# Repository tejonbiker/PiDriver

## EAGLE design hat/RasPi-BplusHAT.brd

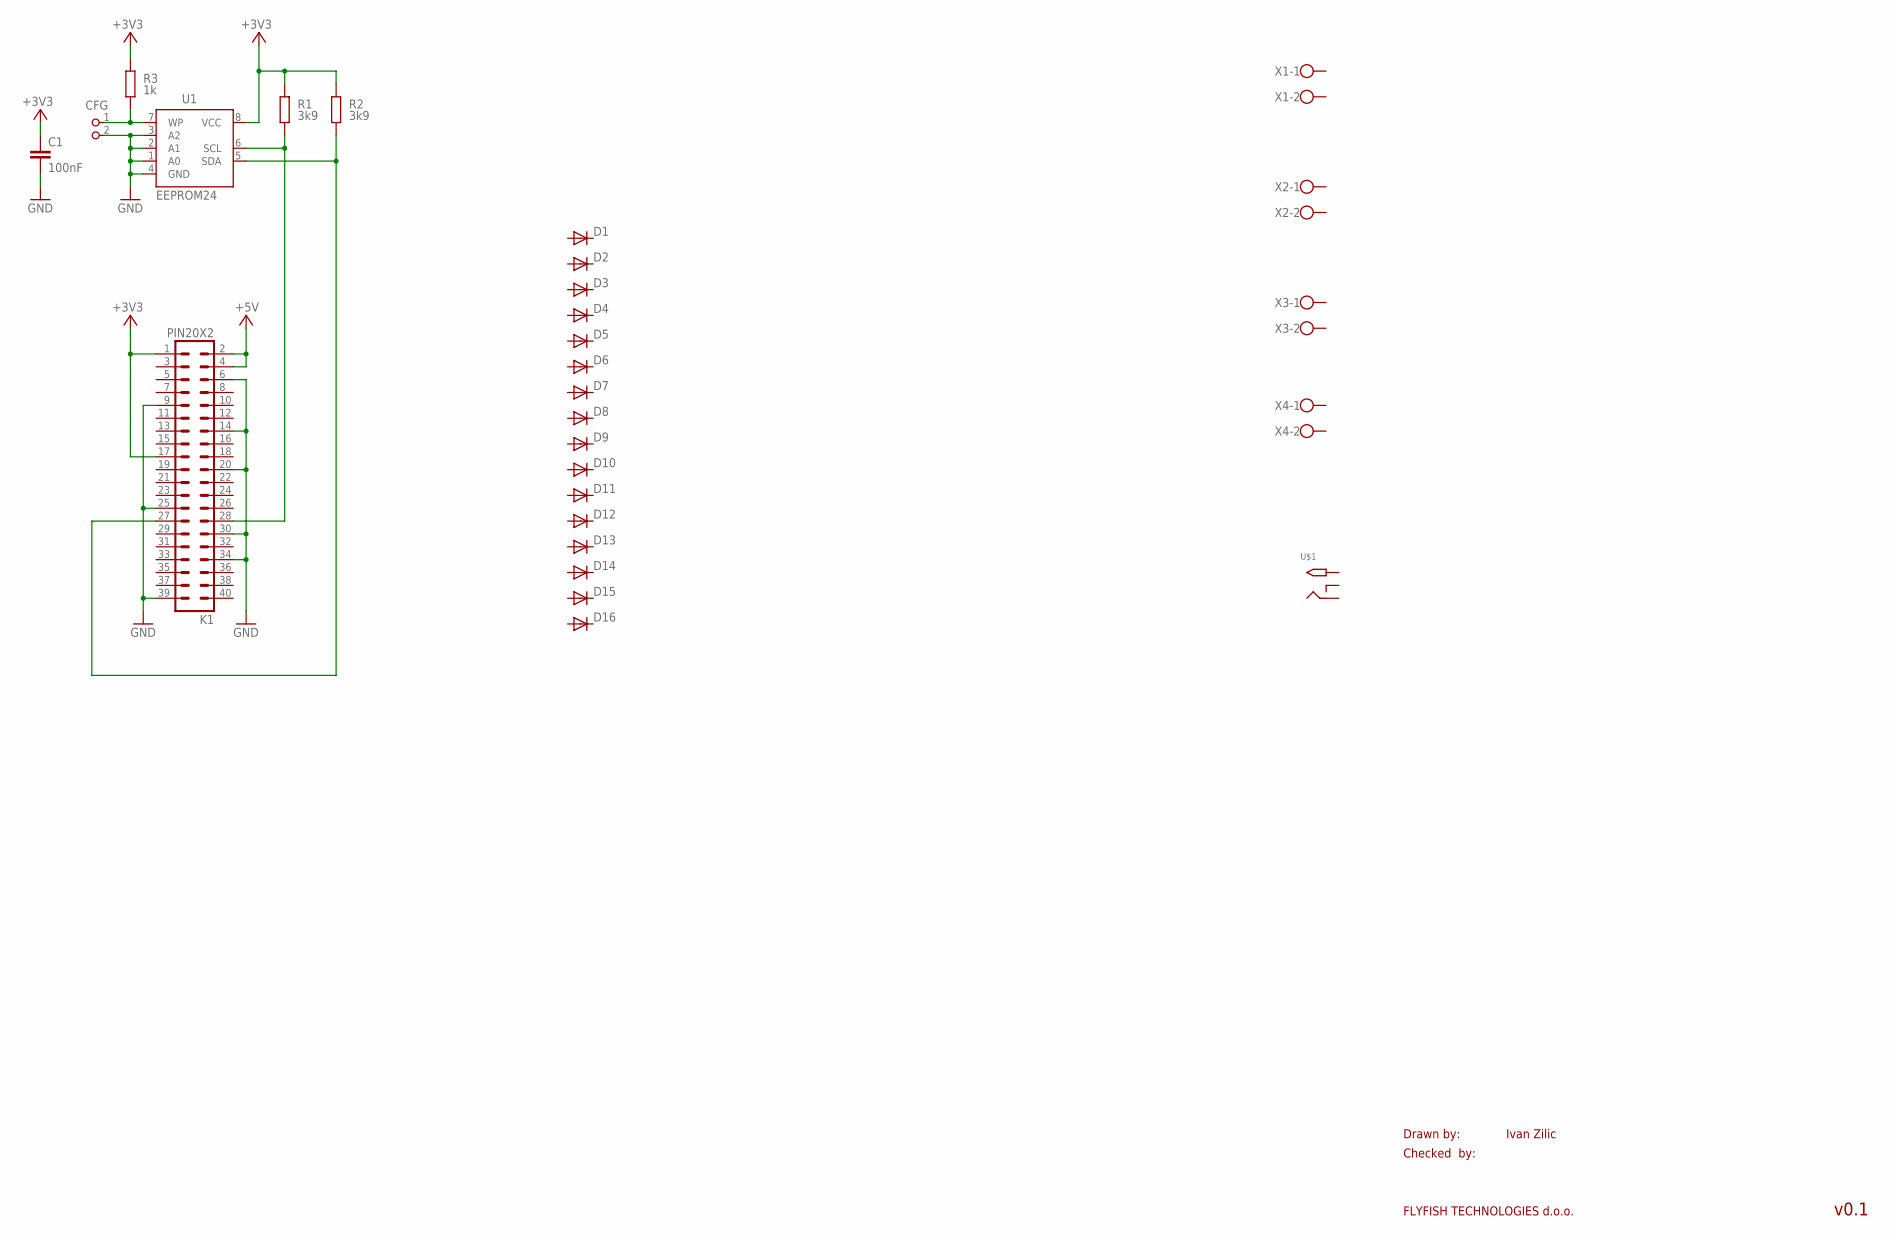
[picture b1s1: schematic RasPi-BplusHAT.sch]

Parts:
C1: 100nF; C0805K
CFG: PIN2_100; PIN_W_2
D1, D2, D3, D4, D5, D6, D7, D8, D9, D10, D11, D12, D13, D14, D15, D16: DIODE-DO-214AC; DO-214AC
K1: PIN20X2; PIN_20X2
R1, R2: 3k9; M0805; TOLERANCE 5%
R3: 1k; M0805; TOLERANCE 5%
U1: EEPROM24; SOIC8
U$1: 2.1MMJACKTHM; PJ-102A
X1, X2, X3, X4: W237-102

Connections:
+3V3: C1.1, K1.1, K1.17, R1.2, R2.2, R3.2, U1.8 (VCC)
+5V: K1.2, K1.4
GND: C1.2, CFG.2, K1.6, K1.9, K1.14, K1.20, K1.25, K1.30, K1.34, K1.39, U1.1 (A0), U1.2 (A1), U1.3 (A2), U1.4 (GND)
unnamed: K1.28, R1.1, U1.6 (SCL)
unnamed: K1.27, R2.1, U1.5 (SDA)
unnamed: CFG.1, R3.1, U1.7 (WP)

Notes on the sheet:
Drawn by:
Checked by:
FLYFISH TECHNOLOGIES d.o.o.
Ivan Zilic
v0.1

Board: 2 copper layers, 28 parts (0 on the bottom side), 6 nets, no tracks yet.

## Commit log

2014-12-17 first commit, the pcb is only a general idea
2014-12-18 the L293E chips was added
2014-12-23 commit de prueba
    subiendo un archivo de prueba
2014-12-23 Revert "commit de prueba"
    This reverts commit 4411ed90550f0cbca264f87b4ffff051d6d5aced.
